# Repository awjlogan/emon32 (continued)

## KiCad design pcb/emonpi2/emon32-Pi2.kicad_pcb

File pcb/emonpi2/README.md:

# emon32-Pi2

_emon32-Pi2_ is a drop in replacement for the [emonPi2](URL HERE!). The main change is the use of a modern high performance microcontroller in place of the aging and expensive AVR parts. Additionally, the firmware moves away from using Arduino as the base environment.

## Changelog

### 0.1

  - Add ADC calibration hardware
  - Add testpoints
  - Move EEPROM and reassign serial modules
  - Add user button, LEDs, external I2C header
  - Safe power negotiation with RPi

### 0.1-dev

  - First bring up of the emon32-Pi2. Directly physically compatible with the existing emonPi2. 
  - Change to 4-layer board
  - Add extra filters and power protection

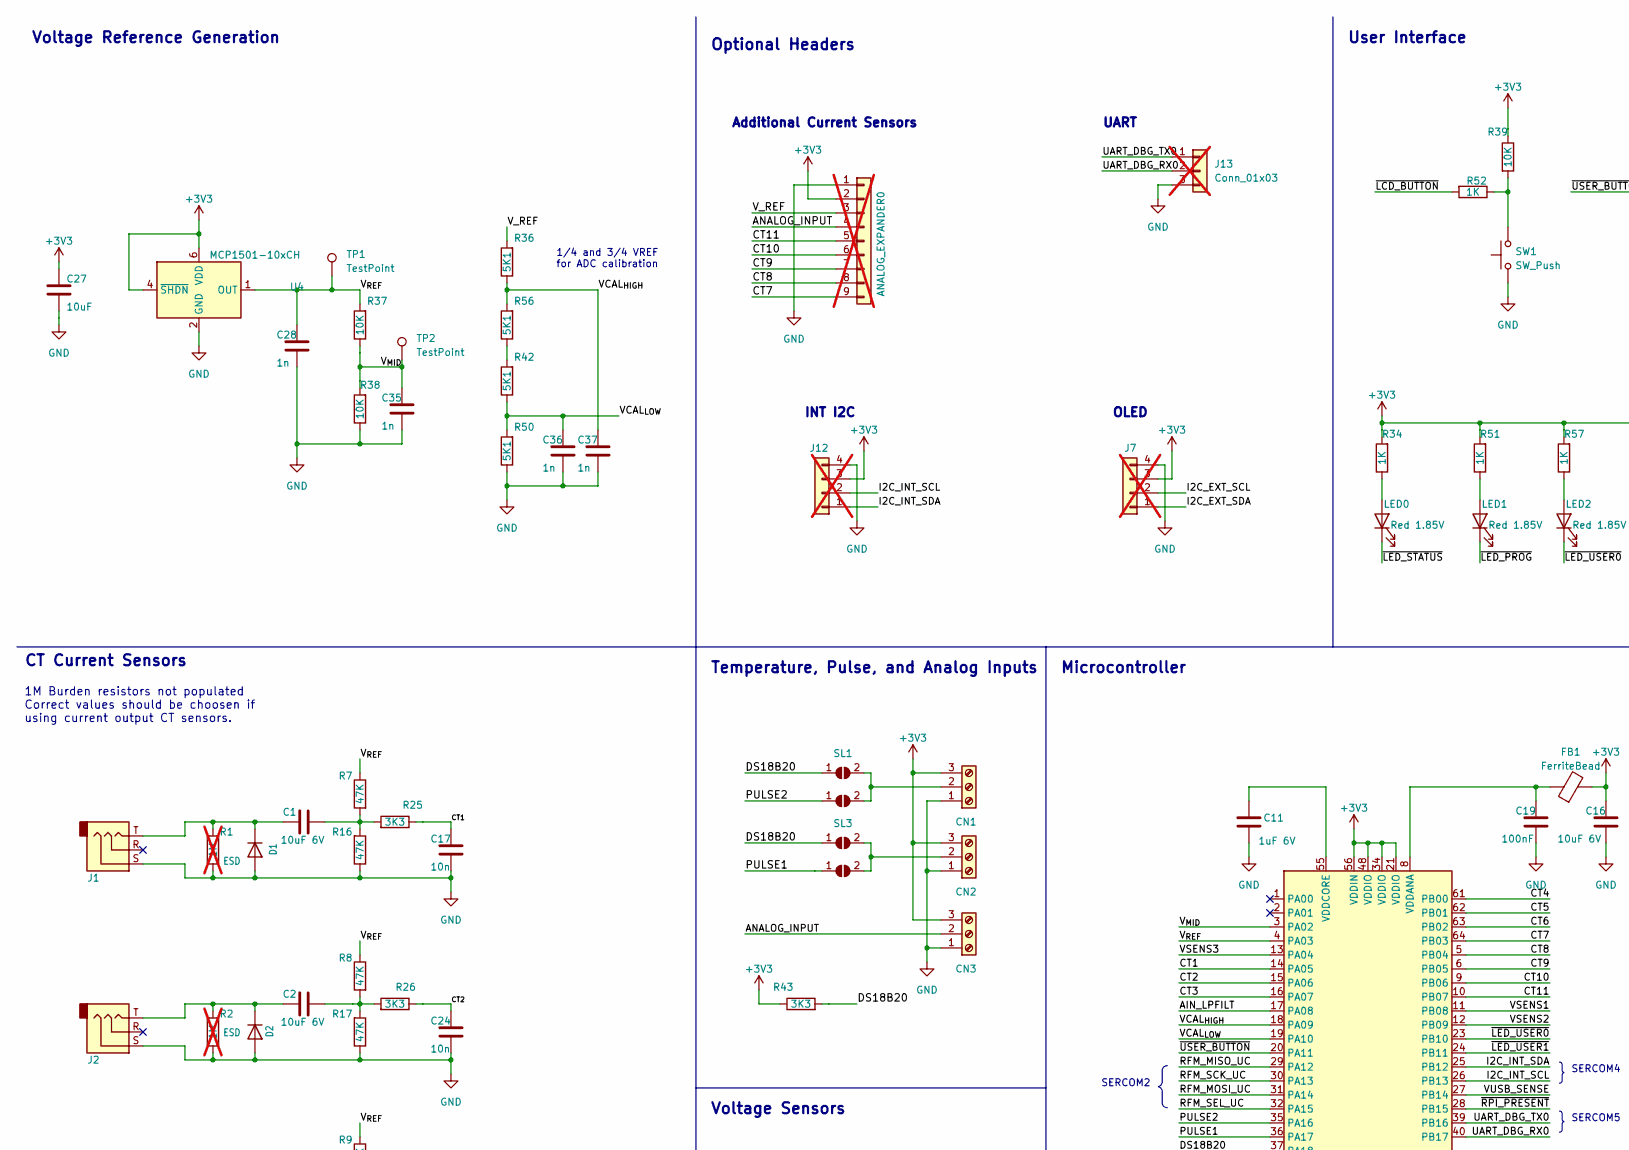
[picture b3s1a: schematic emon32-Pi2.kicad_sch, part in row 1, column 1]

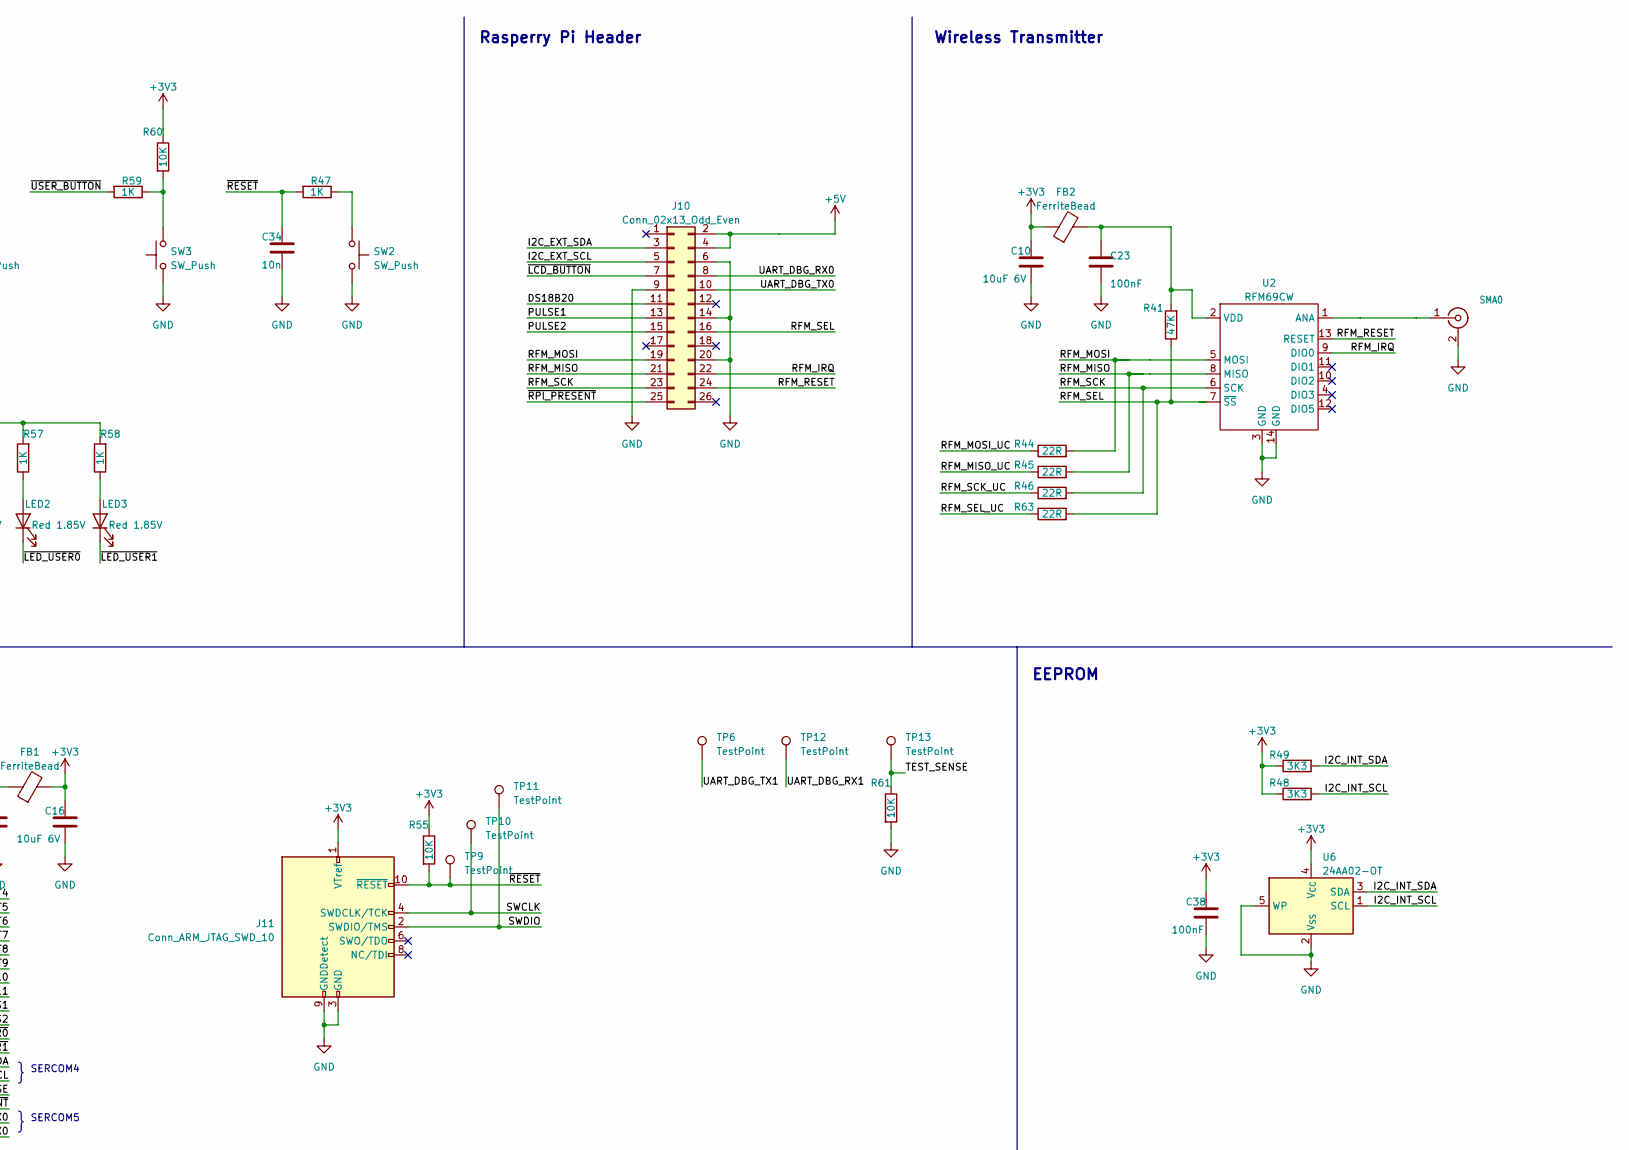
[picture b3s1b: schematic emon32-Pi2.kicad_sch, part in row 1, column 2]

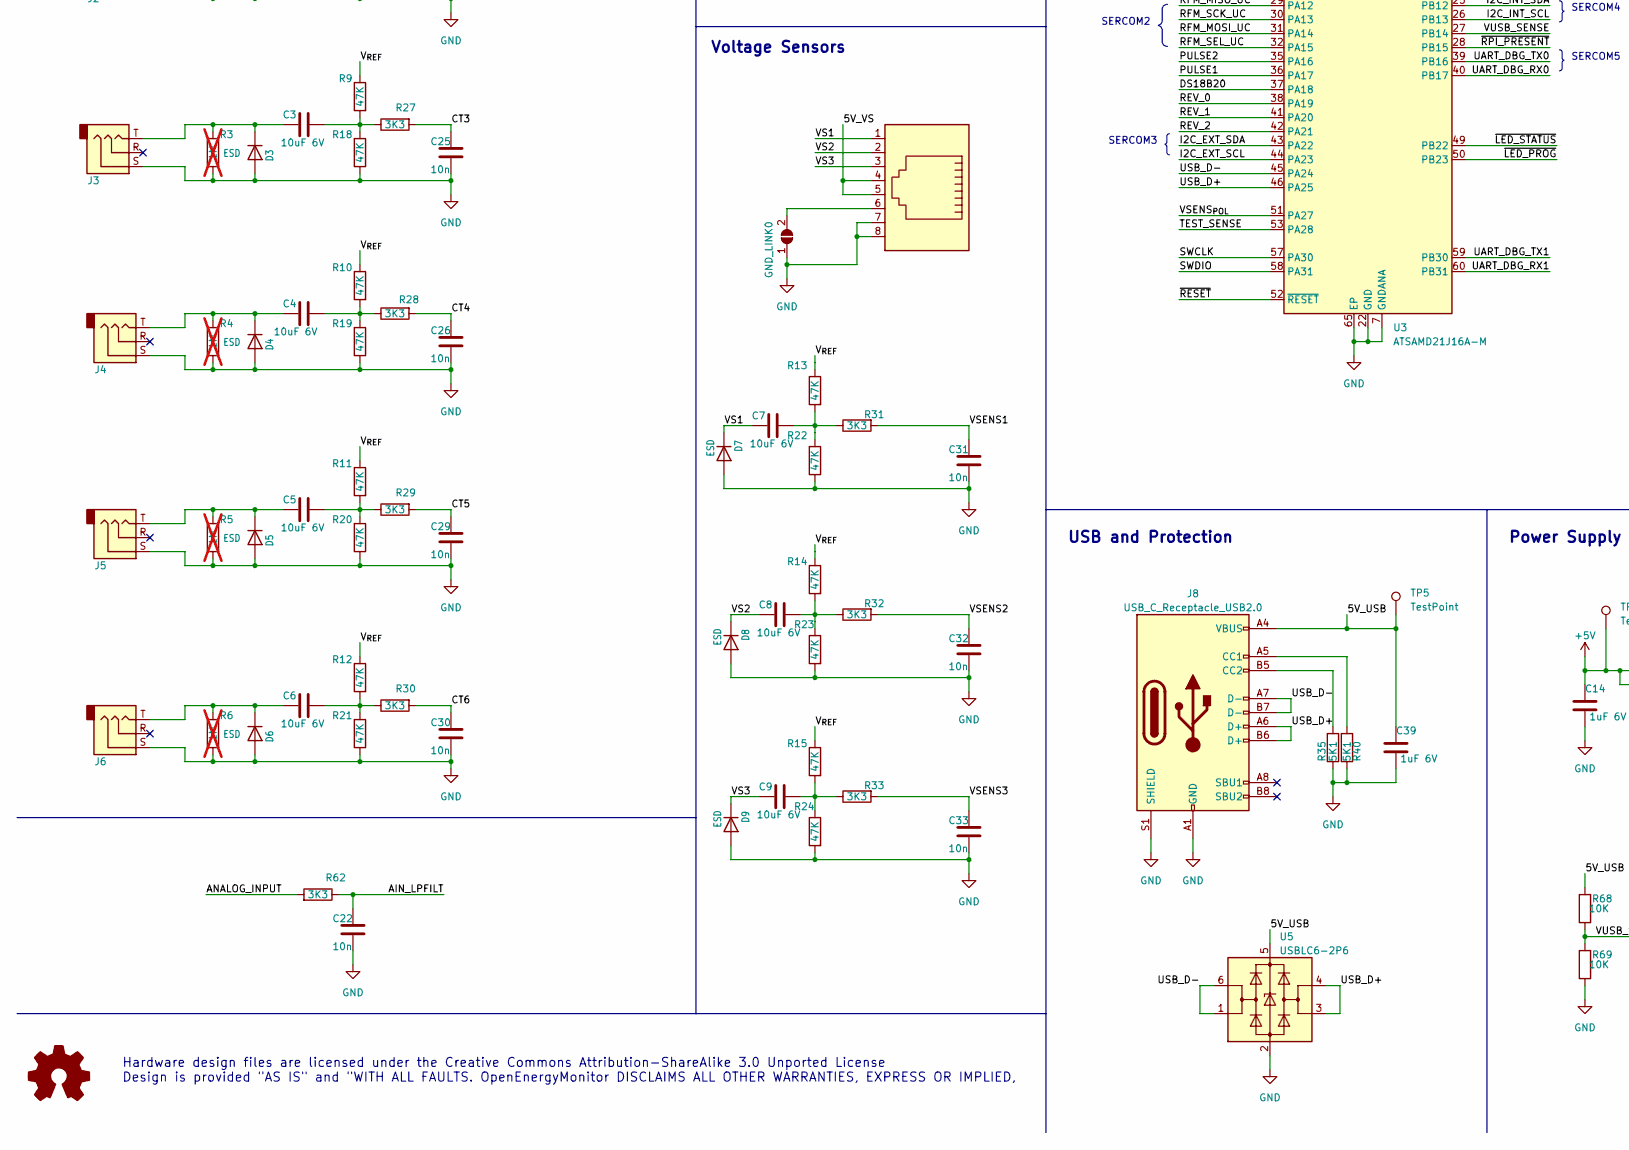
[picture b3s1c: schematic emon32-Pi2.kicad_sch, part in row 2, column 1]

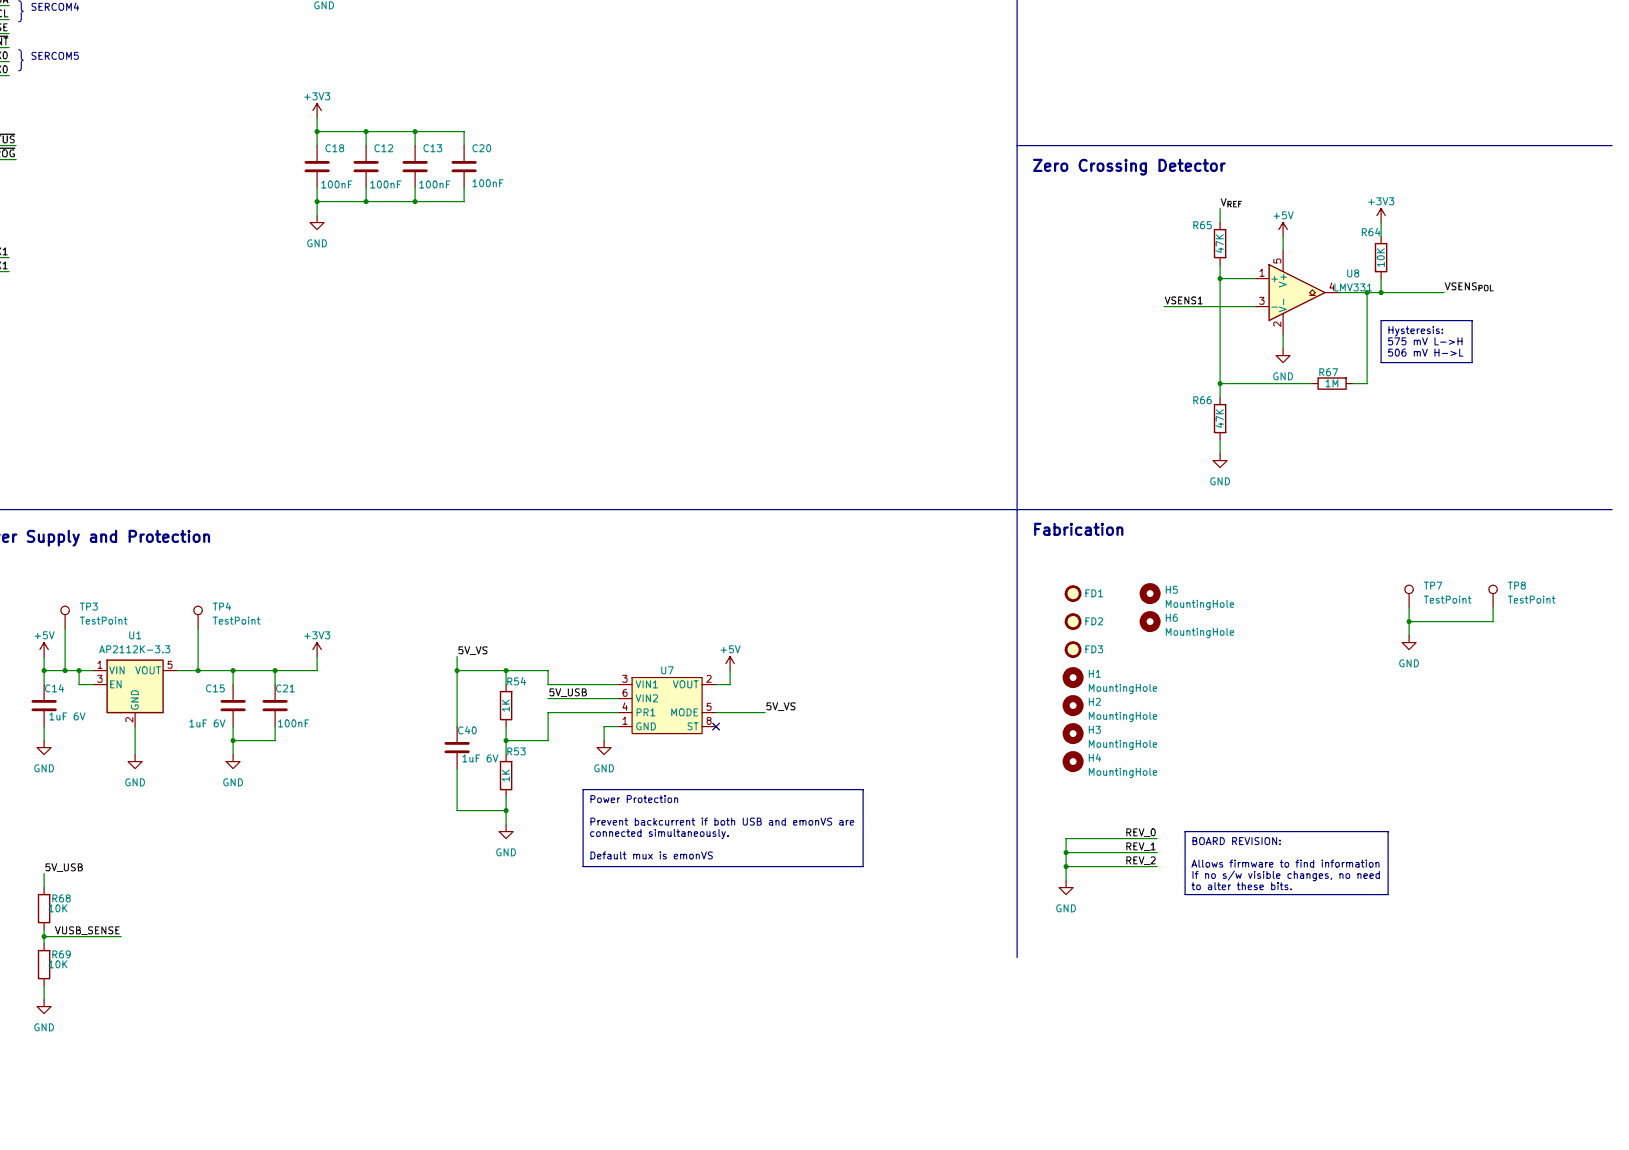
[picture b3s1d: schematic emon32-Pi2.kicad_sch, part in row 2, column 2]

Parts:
ANALOG_EXPANDER0: PINHD-1X9; PinSocket_1x09_P2.54mm_Vertical; not fitted
C1, C2, C3, C4, C5, C6, C7, C8, C9, C10, C16: 10uF 6V; C_0603_1608Metric
C11, C14, C15, C39, C40: 1uF 6V; C_0603_1608Metric
C12, C13, C18, C19, C20, C21, C23, C38: 100nF; C_0603_1608Metric
C17, C22, C24, C25, C26, C29, C30, C31, C32, C33, C34: 10n; C_0603_1608Metric
C27: 10uF; C_0603_1608Metric
C28, C35, C36, C37: 1n; C_0603_1608Metric
CN1, CN2, CN3: CONN_03SCREW; TerminalBlock_Phoenix_PT-1,5-3-3.5-H_1x03_P3.50mm_Horizontal
D1, D2, D3, D4, D5, D6, D7, D8, D9: ESD; D_SOD-523
FB1, FB2: FerriteBead; R_0603_1608Metric
FD1, FD2, FD3: FIDUCIAL1X2; Fiducial_0.75mm_Mask1.5mm
GND_LINK0: SOLDERJUMPERNC; SolderJumper-2_P1.3mm_Open_TrianglePad1.0x1.5mm
H1, H2, H3, H4: MountingHole; MountingHole_2.7mm_M2.5
H5, H6: MountingHole; MountingHole_2.1mm
J1, J2, J3, J4, J5, J6: SJ-3524-SMT-TR; Jack_3.5mm_CUI_SJ-3524-SMT_Horizontal
J7, J12: CONN_04PTH; PinSocket_1x04_P2.54mm_Vertical; not fitted
J8: USB_C_Receptacle_USB2.0; CSP-USC16-TR
J10: Conn_02x13_Odd_Even; PinSocket_2x13_P2.54mm_Vertical
J11: Conn_ARM_JTAG_SWD_10; PinHeader_2x05_P1.27mm_Vertical
J13: Conn_01x03; PinHeader_1x03_P2.54mm_Vertical; not fitted
LED0, LED1, LED2, LED3: Red 1.85V; LED_0805_2012Metric
R1, R2, R3, R4, R5, R6: 1M; R_1206_3216Metric; not fitted
R7, R8, R9, R10, R11, R12, R13, R14, R15, R16, R17, R18, R19, R20, R21, R22, R23, R24, R41, R65, R66: 47K; R_0603_1608Metric
R25, R26, R27, R28, R29, R30, R31, R32, R33, R43, R48, R49, R62: 3K3; R_0603_1608Metric
R34, R47, R51, R52, R53, R54, R57, R58, R59: 1K; R_0603_1608Metric
R35, R36, R40, R42, R50, R56: 5K1; R_0603_1608Metric
R37, R38, R39, R55, R60, R61, R64, R68, R69: 10K; R_0603_1608Metric
R44, R45, R46, R63: 22R; R_0603_1608Metric
R67: 1M; R_0603_1608Metric
RJ45: RJ45-8PTH; RJ45_Amphenol_54602-x08_Horizontal
SL1, SL3: JUMPER-SMT_2_NC_PASTE_NO-SILK; SolderJumper-2_P1.3mm_Open_TrianglePad1.0x1.5mm
SL2, SL4: SOLDERJUMPERNC; SolderJumper-2_P1.3mm_Open_TrianglePad1.0x1.5mm
SMA0: SMACONNECTOR; SMA_Amphenol_132203-12_Horizontal
SW1, SW2, SW3: SW_Push; SW_PUSH_6mm
TP1, TP2, TP3, TP4, TP5, TP6, TP7, TP8, TP9, TP10, TP11, TP12, TP13: TestPoint; TestPoint_Pad_D1.0mm
U1: AP2112K-3.3; SOT-23-5
U2: RFM69CW
U3: ATSAMD21J16A-M; QFN-64-1EP_9x9mm_P0.5mm_EP4.7x4.7mm
U4: MCP1501-10xCH; SOT-23-6
U5: USBLC6-2P6; SOT-666
U6: 24AA02-OT; SOT-23-5
U7: SOT-583-8
U8: LMV331; SOT-23-5

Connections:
+3V3: ANALOG_EXPANDER0.2, C10.1, C12.1, C13.1, C15.2, C16.1, C18.1, C20.1, C21.2, C27.1, C38.1, CN1.3, CN2.3, CN3.3, FB1.2, FB2.1, J7.3, J11.1 (VTref), J12.3, R34.2, R39.1, R43.1, R48.1, R49.1, R51.2, R55.1, R57.2, R58.2, R60.1, R64.1, TP4.1, U1.5 (VOUT), U3.21 (VDDIO), U3.34 (VDDIO), U3.48 (VDDIO), U3.56 (VDDIN), U4.4 (~SHDN), U4.6 (VDD), U6.4 (V_{CC})
+5V: C14.2, J10.2, J10.4, TP3.1, U1.1 (VIN), U1.3 (EN), U7.2 (VOUT), U7.7 (VOUT), U8.5 (V+)
/5V_USB: C39.2, J8.A4 (VBUS), J8.A9 (VBUS), J8.B4 (VBUS), J8.B9 (VBUS), R68.2, TP5.1, U5.5 (VBUS), U7.6 (VIN2)
/5V_VS: C40.2, R54.2, RJ45.4, RJ45.5, U7.3 (VIN1), U7.5 (MODE)
/AIN_LPFILT: C22.1, R62.1, U3.17 (PA08)
/ANALOG_INPUT: ANALOG_EXPANDER0.4, CN3.2, R62.2
/CT1: C17.1, R25.1, U3.14 (PA05)
/CT2: C24.1, R26.1, U3.15 (PA06)
/CT3: C25.1, R27.2, U3.16 (PA07)
/CT4: C26.1, R28.2, U3.61 (PB00)
/CT5: C29.1, R29.2, U3.62 (PB01)
/CT6: C30.1, R30.2, U3.63 (PB02)
/CT7: ANALOG_EXPANDER0.9, U3.64 (PB03)
/CT8: ANALOG_EXPANDER0.8, U3.5 (PB04)
/CT9: ANALOG_EXPANDER0.7, U3.6 (PB05)
/CT10: ANALOG_EXPANDER0.6, U3.9 (PB06)
/CT11: ANALOG_EXPANDER0.5, U3.10 (PB07)
/DS18B20: J10.11, R43.2, SL1.1 (A), SL3.1 (A), U3.37 (PA18)
/I2C_EXT_SCL: J7.2, J10.5, U3.44 (PA23)
/I2C_EXT_SDA: J7.1, J10.3, U3.43 (PA22)
/I2C_INT_SCL: J12.2, R48.2, U3.26 (PB13), U6.1 (SCL)
/I2C_INT_SDA: J12.1, R49.2, U3.25 (PB12), U6.3 (SDA)
/PULSE1: J10.13, SL4.1 (A), U3.36 (PA17)
/PULSE2: J10.15, SL2.1 (A), U3.35 (PA16)
/RFM_IRQ: J10.22, U2.9 (DIO0)
/RFM_MISO: J10.21, R45.2, U2.8 (MISO)
/RFM_MISO_UC: R45.1, U3.29 (PA12)
/RFM_MOSI: J10.19, R44.2, U2.5 (MOSI)
/RFM_MOSI_UC: R44.1, U3.31 (PA14)
/RFM_RESET: J10.24, U2.13 (RESET)
/RFM_SCK: J10.23, R46.2, U2.6 (SCK)
/RFM_SCK_UC: R46.1, U3.30 (PA13)
/RFM_SEL: J10.16, R41.1, R63.2, U2.7 (~SS)
/RFM_SEL_UC: R63.1, U3.32 (PA15)
/SWCLK: J11.4 (SWDCLK/TCK), TP10.1, U3.57 (PA30)
/SWDIO: J11.2 (SWDIO/TMS), TP11.1, U3.58 (PA31)
/TEST_SENSE: R61.1, TP13.1, U3.53 (PA28)
/UART_DBG_RX0: J10.8, J13.2, U3.40 (PB17)
/UART_DBG_RX1: TP12.1, U3.60 (PB31)
/UART_DBG_TX0: J10.10, J13.1, U3.39 (PB16)
/UART_DBG_TX1: TP6.1, U3.59 (PB30)
/USB_D+: J8.A6 (D+), J8.B6 (D+), U3.46 (PA25), U5.3 (I/O2), U5.4 (I/O2)
/USB_D-: J8.A7 (D-), J8.B7 (D-), U3.45 (PA24), U5.1 (I/O1), U5.6 (I/O1)
/VCAL_{HIGH}: C37.1, R36.1, R56.2, U3.18 (PA09)
/VCAL_{LOW}: C36.1, R42.1, R50.2, U3.19 (PA10)
/VS1: C7.1, D7.1 (K), RJ45.1
/VS2: C8.1, D8.1 (K), RJ45.2
/VS3: C9.1, D9.1 (K), RJ45.3
/VSENS1: C31.1, R31.2, U3.11 (PB08), U8.3 (-)
/VSENS2: C32.1, R32.2, U3.12 (PB09)
/VSENS3: C33.1, R33.2, U3.13 (PA04)
/VSENS_{POL}: R64.2, R67.2, U3.51 (PA27), U8.4
/VUSB_SENSE: R68.1, R69.2, U3.27 (PB14)
/V_REF: ANALOG_EXPANDER0.3, R36.2
/V_{MID}: C35.1, R37.1, R38.2, TP2.1, U3.3 (PA02)
/V_{REF}: C28.1, R7.1, R8.1, R9.1, R10.1, R11.1, R12.1, R13.1, R14.1, R15.1, R37.2, R65.1, TP1.1, U3.4 (PA03), U4.1 (OUT)
/~LCD_BUTTON: J10.7, R52.2
/~LED_PROG: LED1.1 (K), U3.50 (PB23)
/~LED_STATUS: LED0.1 (K), U3.49 (PB22)
/~LED_USER0: LED2.1 (K), U3.23 (PB10)
/~LED_USER1: LED3.1 (K), U3.24 (PB11)
/~RESET: C34.1, J11.10 (~RESET), R47.2, R55.2, TP9.1, U3.52 (~RESET)
/~RPI_PRESENT: J10.25, U3.28 (PB15)
/~USER_BUTTON: R59.2, U3.20 (PA11)
GND: ANALOG_EXPANDER0.1, C10.2, C11.2, C12.2, C13.2, C14.1, C15.1, C16.2, C17.2, C18.2, C19.2, C20.2, C21.1, C22.2, C23.2, C24.2, C25.2, C26.2, C27.2, C28.2, C29.2, C30.2, C31.2, C32.2, C33.2, C34.2, C35.2, C36.2, C37.2, C38.2, C39.1, C40.1, CN1.1, CN2.1, CN3.1, D1.2 (A), D2.2 (A), D3.2 (A), D4.2 (A), D5.2 (A), D6.2 (A), D7.2 (A), D8.2 (A), D9.2 (A), GND_LINK0.1 (A), J1.S, J2.S, J3.S, J4.S, J5.S, J6.S, J7.4, J8.A1 (GND), J8.A12 (GND), J8.B1 (GND), J8.B12 (GND), J8.S1 (SHIELD), J10.6, J10.9, J10.14, J10.20, J11.3 (GND), J11.5 (GND), J11.9 (GNDDetect), J12.4, J13.3, R1.2, R2.2, R3.2, R4.2, R5.2, R6.2, R16.1, R17.1, R18.1, R19.1, R20.1, R21.1, R22.1, R23.2, R24.2, R35.1, R38.1, R40.1, R50.1, R53.1, R61.2, R66.2, R69.1, RJ45.7, RJ45.8, SMA0.2 (Ext), SW1.1, SW2.2, SW3.1, TP7.1, TP8.1, U1.2 (GND), U2.3 (GND), U2.14 (GND), U3.7 (GNDANA), U3.22 (GND), U3.33 (GND), U3.38 (PA19), U3.41 (PA20), U3.42 (PA21), U3.47 (GND), U3.54 (GND), U3.65 (EP), U4.2 (GND), U4.3 (GND), U4.5 (GND), U5.2 (GND), U6.2 (V_{SS}), U6.5 (WP), U7.1 (GND), U8.2 (V-)
unnamed: C1.2, R7.2, R16.2, R25.2
unnamed: C2.2, R8.2, R17.2, R26.2
unnamed: C3.2, R9.2, R18.2, R27.1
unnamed: C4.2, R10.2, R19.2, R28.1
unnamed: C5.2, R11.2, R20.2, R29.1
unnamed: C6.2, R12.2, R21.2, R30.1
unnamed: C7.2, R13.2, R22.2, R31.1
unnamed: C8.2, R14.2, R23.1, R32.1
unnamed: C9.2, R15.2, R24.1, R33.1
unnamed: CN1.2, SL1.2 (B), SL2.2 (B)
unnamed: CN2.2, SL3.2 (B), SL4.2 (B)
unnamed: C1.1, D1.1 (K), J1.T, R1.1
unnamed: C2.1, D2.1 (K), J2.T, R2.1
unnamed: C3.1, D3.1 (K), J3.T, R3.1
unnamed: C4.1, D4.1 (K), J4.T, R4.1
unnamed: C5.1, D5.1 (K), J5.T, R5.1
unnamed: C6.1, D6.1 (K), J6.T, R6.1
unnamed: GND_LINK0.2 (B), RJ45.6
unnamed: J8.A5 (CC1), R40.2
unnamed: J8.B5 (CC2), R35.2
unnamed: LED0.2 (A), R34.1
unnamed: LED1.2 (A), R51.1
unnamed: LED2.2 (A), R57.1
unnamed: LED3.2 (A), R58.1
unnamed: R39.2, R52.1, SW1.2
unnamed: R42.2, R56.1
unnamed: R47.1, SW2.1
unnamed: R59.1, R60.2, SW3.2
unnamed: SMA0.1 (In), U2.1 (ANA)
unnamed: C23.1, FB2.2, R41.2, U2.2 (VDD)
unnamed: C19.1, FB1.1, U3.8 (VDDANA)
unnamed: C11.1, U3.55 (VDDCORE)
unnamed: R53.2, R54.1, U7.4 (PR1)
unnamed: R65.2, R66.1, R67.1, U8.1 (+)

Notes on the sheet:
Power Protection Prevent backcurrent if both USB and emonVS are connected simultaneously. Default mux is emonVS
Hysteresis: 575 mV L->H 506 mV H->L
BOARD REVISION: Allows firmware to find information If no s/w visible changes, no need to alter these bits.
Rasperry Pi Header
Power Supply and Protection
Temperature, Pulse, and Analog Inputs
Hardware design files are licensed under the Creative Commons Attribution-ShareAlike 3.0 Unported License Design is provided "AS IS" and "WITH ALL FAULTS. OpenEnergyMonitor DISCLAIMS ALL OTHER WARRANTIES, EXPRESS OR IMPLIED,
Microcontroller
1/4 and 3/4 VREF for ADC calibration
Zero Crossing Detector
User Interface
SERCOM5
1M Burden resistors not populated Correct values should be choosen if using current output CT sensors.
Voltage Reference Generation
Additional Current Sensors
SERCOM3
UART
USB and Protection
EEPROM
INT I2C
Fabrication
OLED
SERCOM4
Voltage Sensors
CT Current Sensors
SERCOM2
Optional Headers
Wireless Transmitter

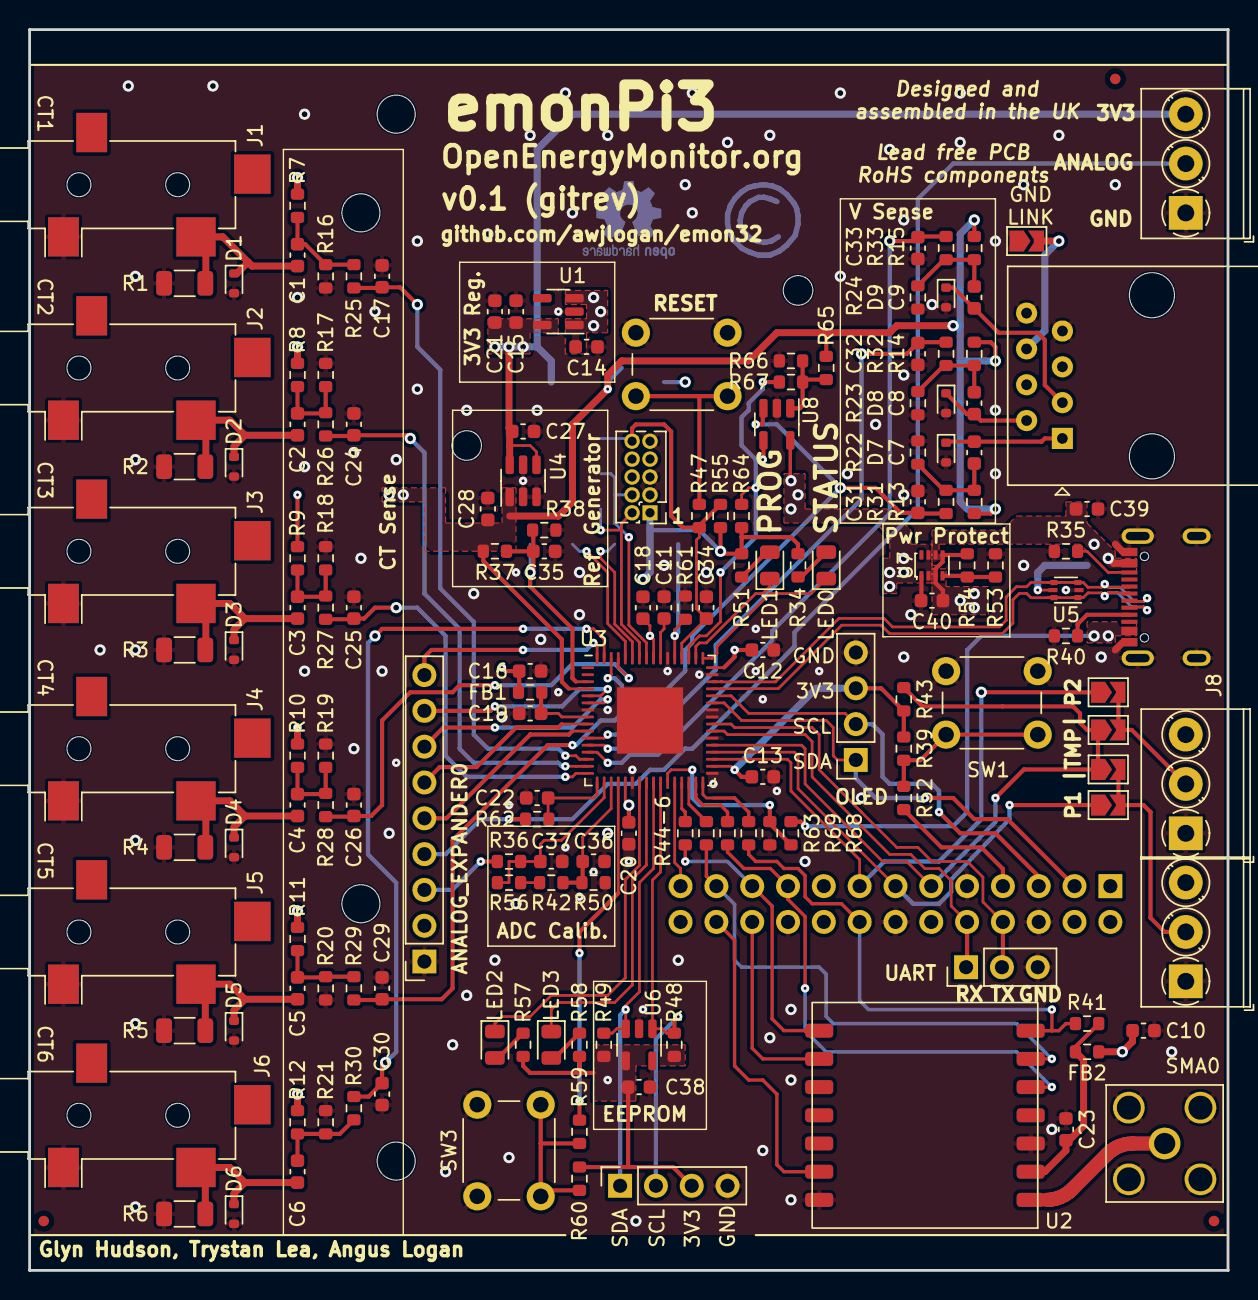
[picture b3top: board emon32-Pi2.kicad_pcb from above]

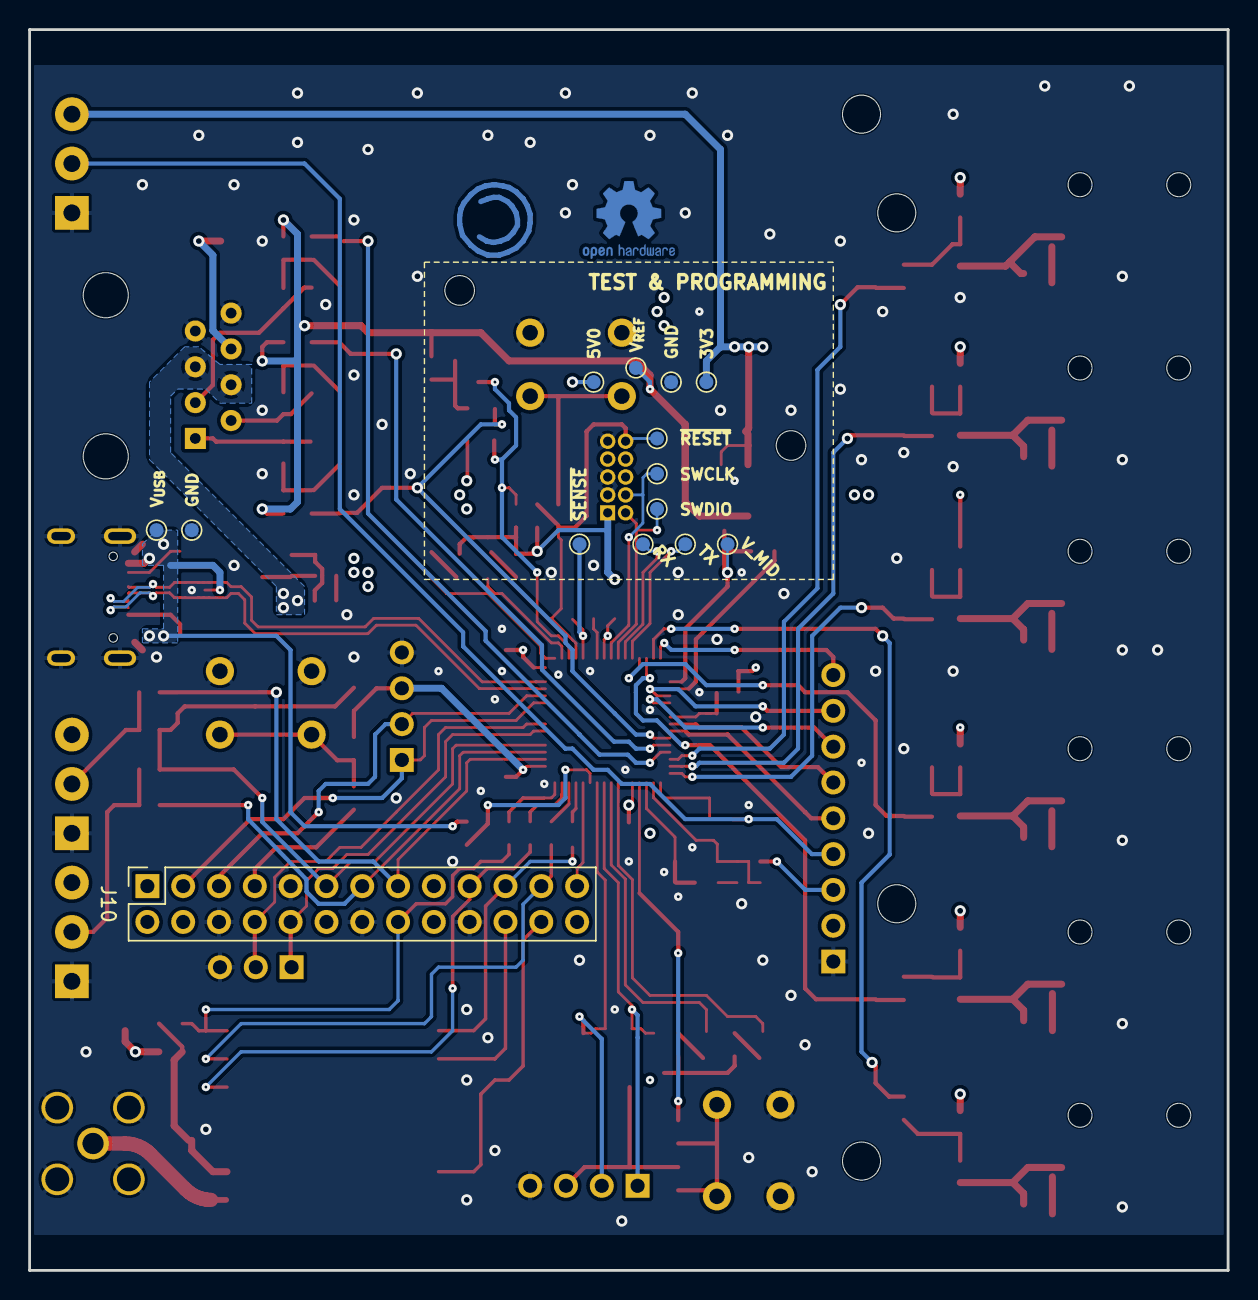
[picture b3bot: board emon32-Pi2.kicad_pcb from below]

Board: 4 copper layers, 85.0 x 88.0 mm, 180 parts (14 on the bottom side), 99 nets.

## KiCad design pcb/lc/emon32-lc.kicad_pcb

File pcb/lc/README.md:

# emon32 Low Cost

## Features

The emon32 Low Cost (emon32-LC) is a minimal implementation of the emon32. It provides the following functions:

  - Single phase voltage monitoring
  - 2X CT channels
  - RFM12/69 **or** ESP8266-01 wireless
  - USB bootloader
  - emon32 debug and configuration UART (8N1 @ 9600 baud)

Headers are available, but are not generally populated, for:

  - Pulse counter **or** OneWire temperature sensor
  - Arm Cortex-M 10 pin SWD header

## Enclosure

The board dimensions are 55x40 mm, with the target enclosure being a 
 
## Configuration

Configuration is typically undertaken through the configuration UART header. With a serial terminal open, 

## Firmware compilation 

### With bootloader

### With no bootloader

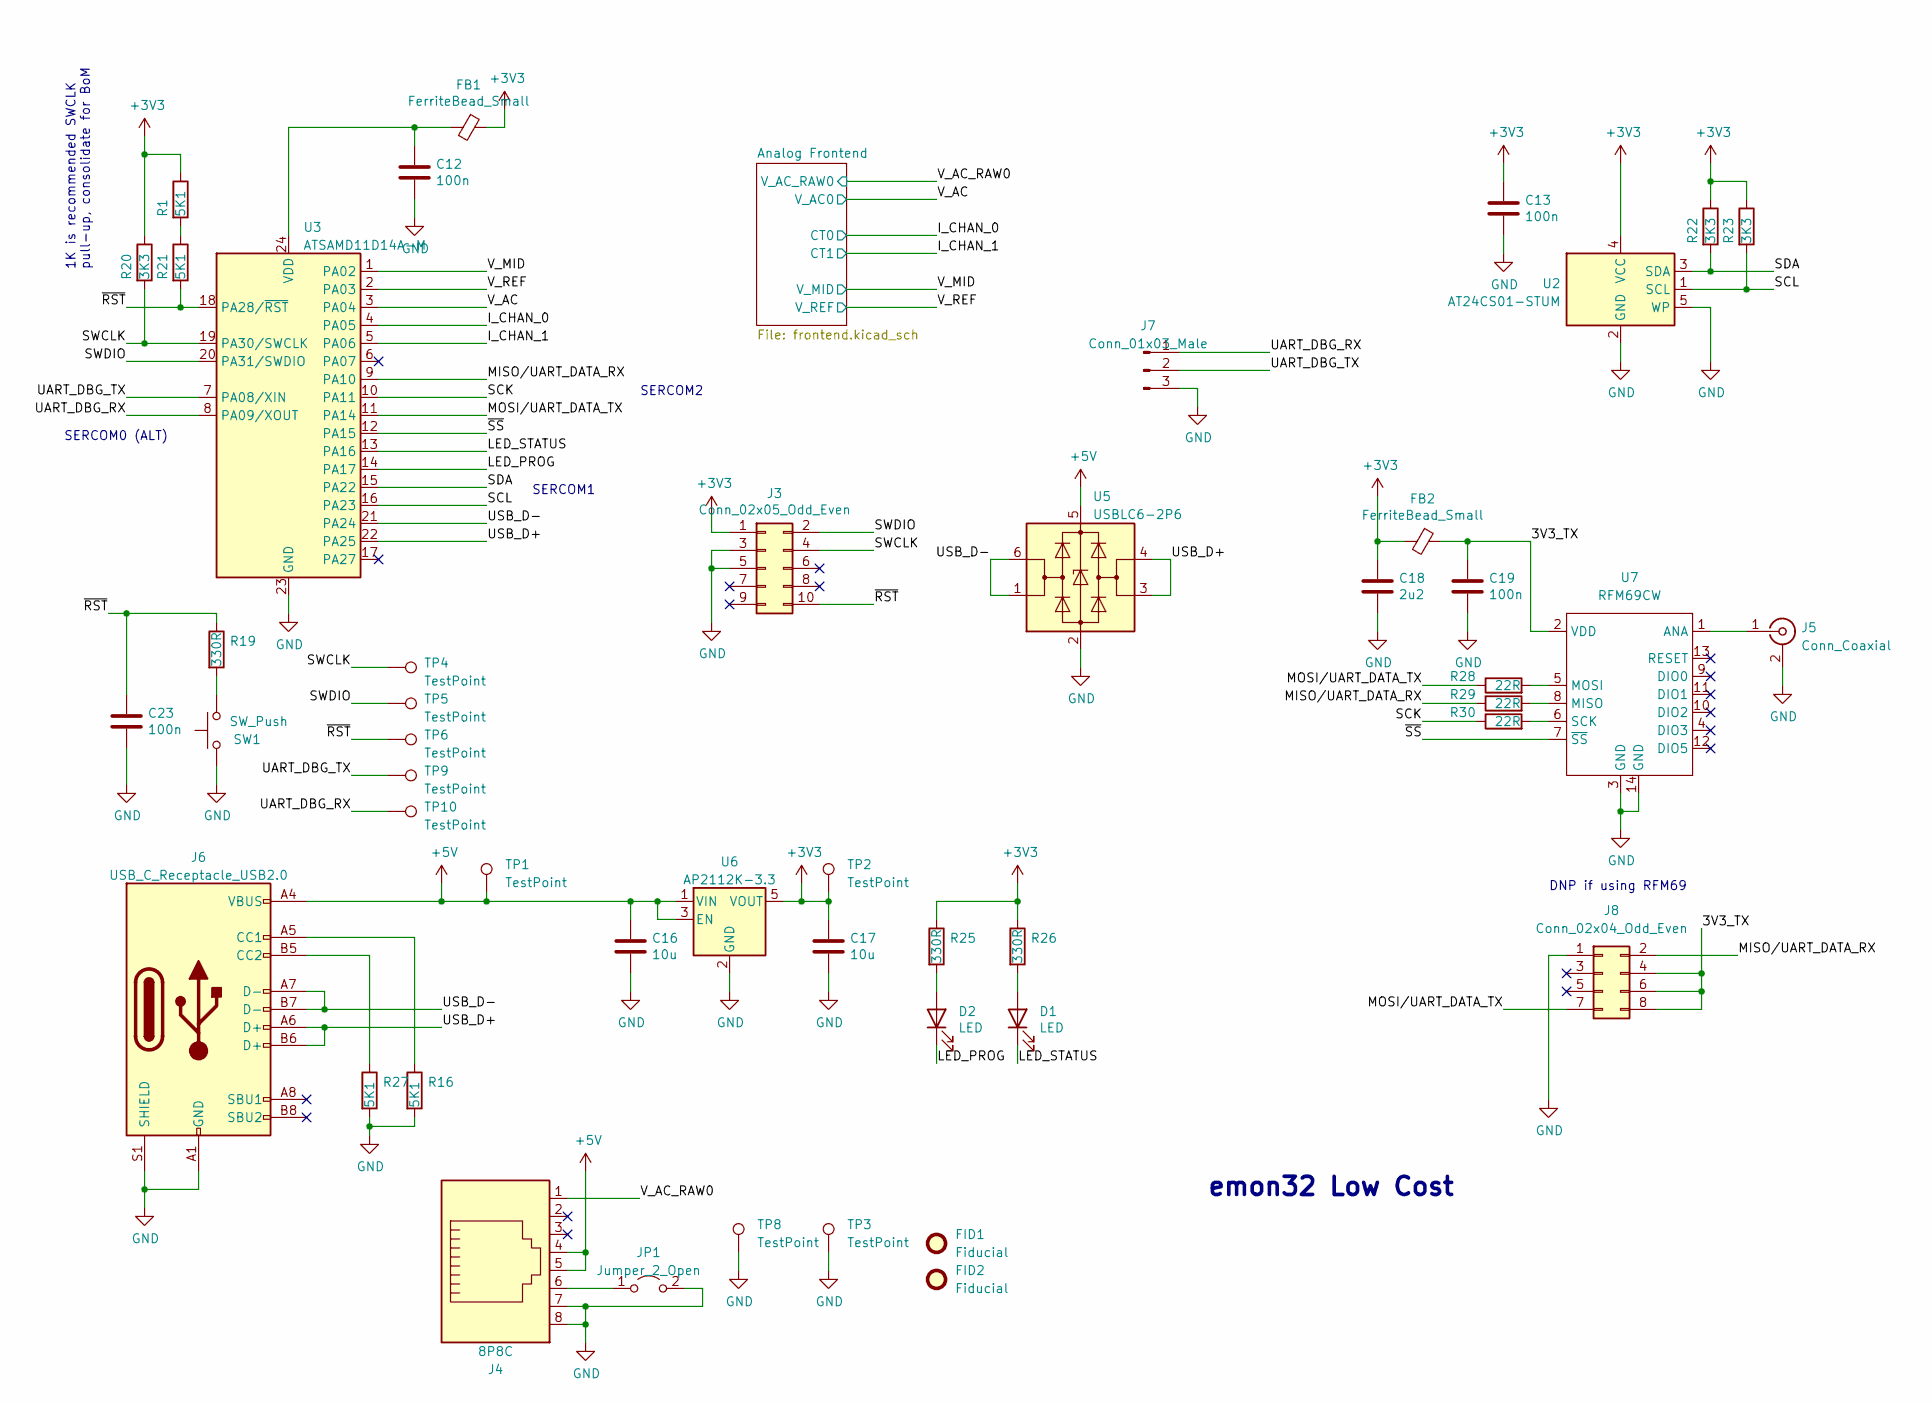
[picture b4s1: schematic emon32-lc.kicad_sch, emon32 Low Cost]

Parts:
C12, C13, C19, C23: 100n; C_0402_1005Metric
C16, C17: 10u; C_0603_1608Metric_Pad1.08x0.95mm_HandSolder
C18: 2u2; C_0603_1608Metric_Pad1.08x0.95mm_HandSolder
D1, D2: LED; LED_0603_1608Metric_Pad1.05x0.95mm_HandSolder
FB1, FB2: FerriteBead_Small; L_0402_1005Metric
FID1, FID2: Fiducial; Fiducial_0.5mm_Mask1mm
J3: Conn_02x05_Odd_Even; PinHeader_2x05_P1.27mm_Vertical
J4: 8P8C; RJ45_Amphenol_54602-x08_Horizontal
J5: Conn_Coaxial; SMA_Amphenol_132203-12_Horizontal
J6: USB_C_Receptacle_USB2.0; CSP-USC16-TR
J7: Conn_01x03_Male; PinHeader_1x03_P2.54mm_Vertical
J8: Conn_02x04_Odd_Even; PinSocket_2x04_P2.54mm_Vertical
JP1: Jumper_2_Open; SolderJumper-2_P1.3mm_Open_TrianglePad1.0x1.5mm
R1, R16, R21, R27: 5K1; R_0402_1005Metric
R19, R25, R26: 330R; R_0402_1005Metric
R20, R22, R23: 3K3; R_0402_1005Metric
R28, R29, R30: 22R; R_0402_1005Metric
SW1: SW_Push; SW_Push_1P1T_NO_CK_KMR2
TP1, TP2, TP3, TP4, TP5, TP6, TP8, TP9, TP10: TestPoint; TestPoint_Pad_D1.5mm
U2: AT24CS01-STUM; SOT-23-5
U3: ATSAMD11D14A-M; QFN-24-1EP_4x4mm_P0.5mm_EP2.6x2.6mm
U5: USBLC6-2P6; SOT-666
U6: AP2112K-3.3; SOT-23-5
U7: RFM69CW

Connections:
+3V3: C13.1, C17.1, C18.1, FB1.1, FB2.2, J3.1, R1.1, R20.1, R22.1, R23.1, R25.1, R26.1, TP2.1, U2.4 (VCC), U6.5 (VOUT); also elsewhere on the board
+5V: C16.1, J4.4, J4.5, J6.A4 (VBUS), J6.A9 (VBUS), J6.B4 (VBUS), J6.B9 (VBUS), TP1.1, U5.5 (VBUS), U6.1 (VIN), U6.3 (EN)
/3V3_TX: C19.1, FB2.1, J8.4, J8.6, J8.8, U7.2 (VDD)
/I_CHAN_0: U3.4 (PA05); also elsewhere on the board
/I_CHAN_1: U3.5 (PA06); also elsewhere on the board
/LED_PROG: D2.1 (K), U3.14 (PA17)
/LED_STATUS: D1.1 (K), U3.13 (PA16)
/MISO/UART_DATA_RX: J8.2, R29.1, U3.9 (PA10)
/MOSI/UART_DATA_TX: J8.7, R28.1, U3.11 (PA14)
/SCK: R30.1, U3.10 (PA11)
/SCL: R23.2, U2.1 (SCL), U3.16 (PA23)
/SDA: R22.2, U2.3 (SDA), U3.15 (PA22)
/SWCLK: J3.4, R20.2, TP4.1, U3.19 (PA30/SWCLK)
/SWDIO: J3.2, TP5.1, U3.20 (PA31/SWDIO)
/UART_DBG_RX: J7.1, TP10.1, U3.8 (PA09/XOUT)
/UART_DBG_TX: J7.2, TP9.1, U3.7 (PA08/XIN)
/USB_D+: J6.A6 (D+), J6.B6 (D+), U3.22 (PA25), U5.3 (I/O2), U5.4 (I/O2)
/USB_D-: J6.A7 (D-), J6.B7 (D-), U3.21 (PA24), U5.1 (I/O1), U5.6 (I/O1)
/V_AC: U3.3 (PA04); also elsewhere on the board
/V_AC_RAW0: J4.1; also elsewhere on the board
/V_MID: U3.1 (PA02); also elsewhere on the board
/V_REF: U3.2 (PA03); also elsewhere on the board
/~RST: C23.1, J3.10, R19.1, R21.2, TP6.1, U3.18 (PA28/~RST)
/~SS: U3.12 (PA15), U7.7 (~SS)
GND: C12.2, C13.2, C16.2, C17.2, C18.2, C19.2, C23.2, J3.3, J3.5, J4.7, J4.8, J5.2 (Ext), J6.A1 (GND), J6.A12 (GND), J6.B1 (GND), J6.B12 (GND), J6.S1 (SHIELD), J7.3, J8.1, JP1.2 (B), R16.2, R27.2, SW1.1, TP3.1, TP8.1, U2.2 (GND), U2.5 (WP), U3.23 (GND), U5.2 (GND), U6.2 (GND), U7.3 (GND), U7.14 (GND); also elsewhere on the board
unnamed: D1.2 (A), R26.2
unnamed: D2.2 (A), R25.2
unnamed: J5.1 (In), U7.1 (ANA)
unnamed: J6.A5 (CC1), R16.1
unnamed: J6.B5 (CC2), R27.1
unnamed: J4.6, JP1.1 (A)
unnamed: R1.2, R21.1
unnamed: R19.2, SW1.2
unnamed: C12.1, FB1.2, U3.24 (VDD)
unnamed: R29.2, U7.8 (MISO)
unnamed: R28.2, U7.5 (MOSI)
unnamed: R30.2, U7.6 (SCK)

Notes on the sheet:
emon32 Low Cost
DNP if using RFM69
1K is recommended SWCLK pull-up, consolidate for BoM
SERCOM2
SERCOM0 (ALT)
SERCOM1
